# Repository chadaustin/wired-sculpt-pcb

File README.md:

# Design Files for Wired Sculpt Conversion Board

This repository contains the schematic and layout files for the [Microsoft Sculpt Wired Conversion Mod](https://chadaustin.me/2021/02/wired-sculpt/).

## Project Updates

### 2021-09-07

The rev5 board design proposal.

Removed the charge pump.
When the common pin for both LEDs is driven with a 50% duty-cycle rectangular signal both LEDs can be used without additional circuit.
QMK has a feature to change the brightness of background LEDs and we are just going to use this feature to produce such a signal.

As the FN switch is also connected to this line we have to filter out the switching frequency to be able to read the switch.
For this a simple diode rectifier was added. A resistor to discharge the filter capacitor is also needed to detect the switch off state.

### 2021-09-07

The rev4 board design is complete.

When I upgraded the 30-pin ribbon connector to one that fit better, it lowered the resistance to the LEDs. This caused me to burn the microcontroller on a test rev3 board by drawing too much current. So the question became: what values are appropriate for "maximum" brightness on both red and green. Today I found that, given a 5.15V VUSB, whatever resistance in the flex cable, and whatever voltage drop on the LEDs, 150 Ohms gives an even brightness on both red and green. Green draws about 15 mA and red about 10 mA, both within USB low-power spec and the current limits on the microcontroller.

I added an [outputs](outputs/) directory containing the different revisions, and gerber files and drill files generated for either PCBWay or OSH Park.

The biggest challenge right now is the chip shortage. Even some of the capacitors I chose are out of stock. The hardest component to acquire is the ESD protection IC: USBLC6-2SC6. The USBLC6-4SC6 is available, but it would require some tweaking to the PCB layout.

On the software side of things, I added an internal ring buffer for debugging the debouncer. It can be dumped to the HID debug channel by holding both shifts and pressing H. I am trying to figure out why, with my custom low-latency debouncer, sometimes "the" comes out as "theb". For anyone that isn't trying to optimize latency as much as me, you can just run with the default QMK debouncer, which I've never seen produce phantom keys.

### 2021-05-02

One thing that annoyed me about the previous board design was that neither LED was hooked up to a PWM-capable pin and that the green one couldn't be driven, since it wants -5V. I want both lights to work and both to be dimmable.

Rev3 includes a charge pump to produce -5V and two MOSFETs that allow switching the green cathode with PWM.

I also figured out how the Fn switch works: it's a resistor divider that toggles 47K pull-down on a pin with a permanent 1M pull-up. Rev3 includes said 1M pull-up, so the firmware can read the Fn switch's state.

Sadly, it looks like there were many arrangements of media keys on the Sculpt over the years, and most of the media keys have nonsensical icons with behavior that differs on each platform. I'll try to make at least volume and play/pause work.

The parts for board rev 3 arrived last week. Some adjustments were required due to the chip shortage, but it's not too bad. The microcontroller is still available at least.

I attempted assembly of one, and it worked fine, but I screwed up the red and green pins, so I cut some traces and bodged in some kynar wire.

Both lights work!

I have not tested PWM. I did observe that twice as much current is being drawn for each light as I expected. I fear 40 mA could burn out the lights, so I plan to measure an appropriate series resistor this week. It's possible I never had this problem before because I was using a worse-fitting ribbon connector previously. In the past, I always measured 100 Ohms on every pin, but never tested the new ribbon connector.

Also, it kind of sucks that the LED brightness is a function of USB voltage (anywhere between 4.6 V and 5.25 V), but I don't want to include a regulator...

Assembly took about five hours for one board. A lot of that was getting my desk set up. I imagine I could do three boards in ... eight? I think if I used a stencil, hot air assembly could go pretty quickly. Especially if I had a preheater like the MHP30.

A couple people have suggested I set up an Etsy, but if I properly priced in hours of my labor, it would get prohibitive. And I don't want to deal with returns and warranties.

Remaining items before I can say the board is done:
* Order a fourth PCB design with fixed green and red pins
* Include an 0603 resistor on each
* Fix the debouncer
* Add a media key QMK layer, enabled with the Fn switch.

### 2021-04-27

In February, I tried pushing latency further than QMK offers out of the box. I switched from the default debouncer to sym_eager_pk, but since then I've observed some false keydowns and occasionally a phantom keypress. It's common for "the" to produce "theb". (Note that I use the Dvorak key layout.) I haven't looked at the matrix, but it's clear some debouncing is needed on keydown.

I'm planning on writing a custom debouncer that requires at least two frames for a keydown to register and at least 10 ms for a keyup. Having never done AVR optimization, I am trying to get a [simavr](https://github.com/buserror/simavr) benchmark harness up to make sure I don't regress the scan rate.

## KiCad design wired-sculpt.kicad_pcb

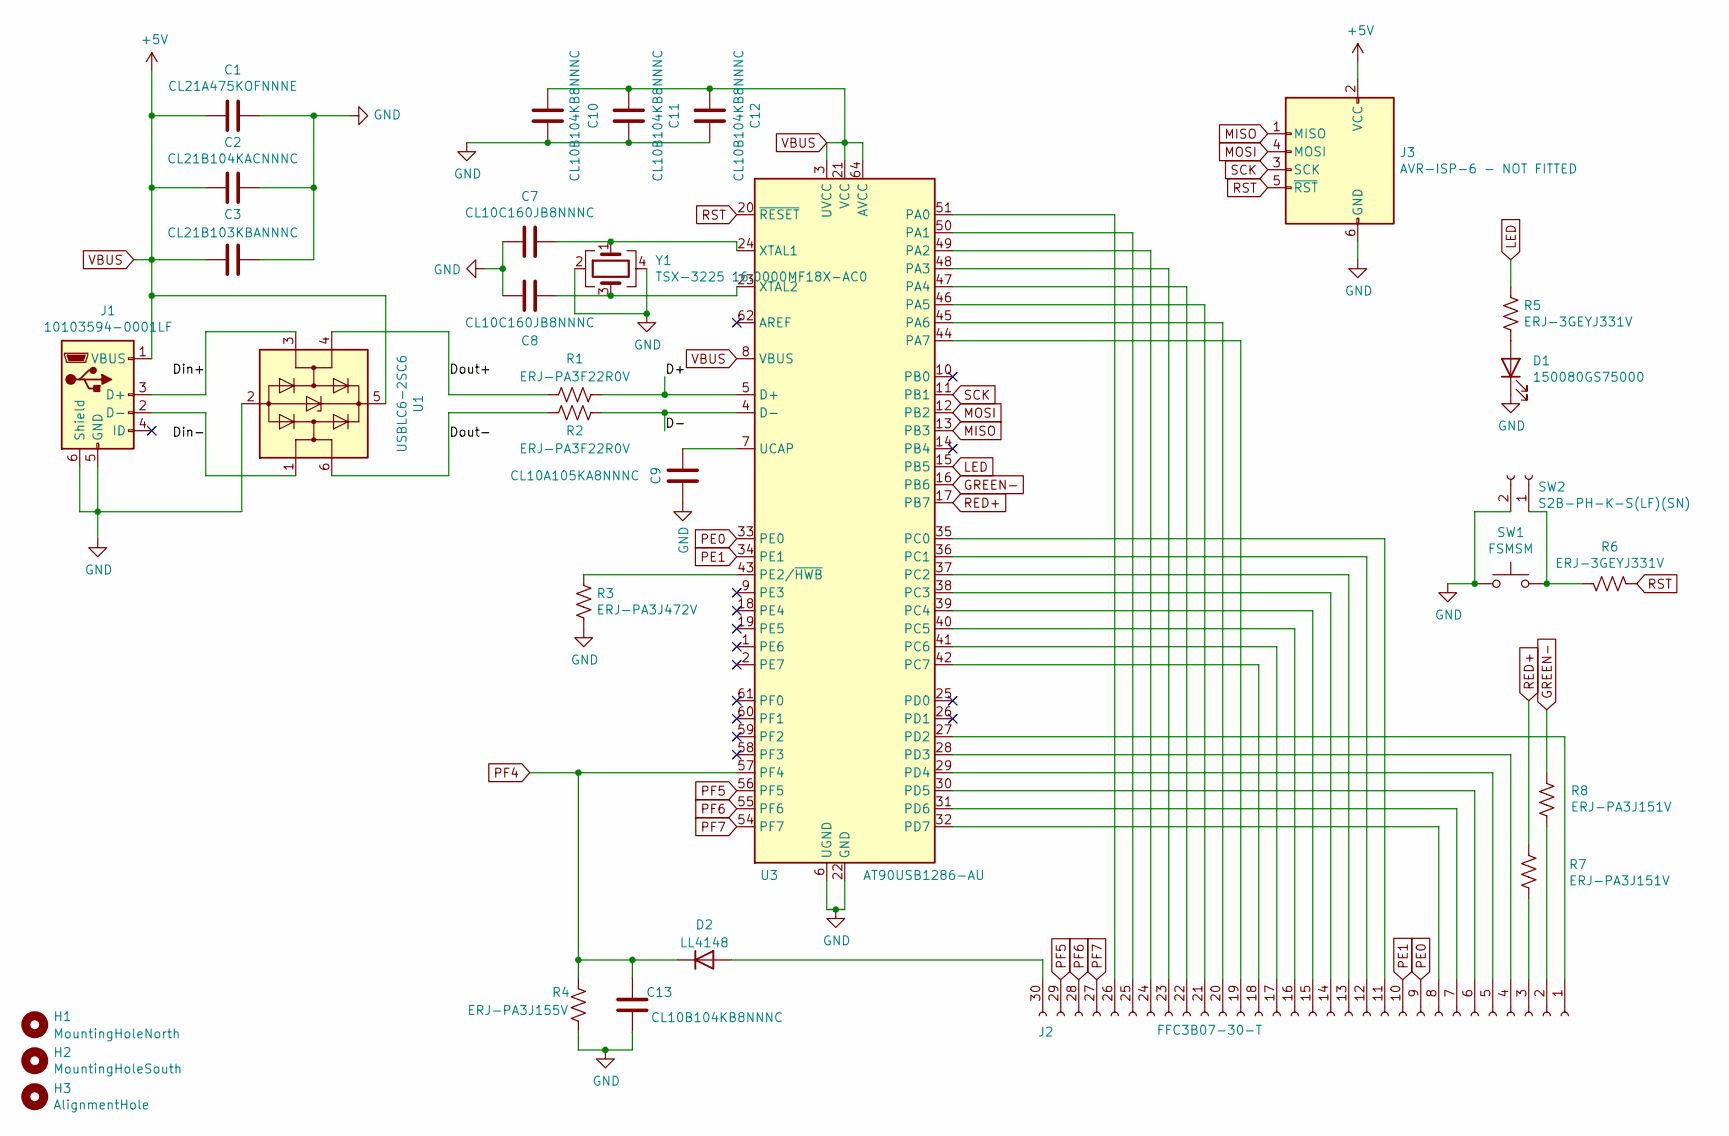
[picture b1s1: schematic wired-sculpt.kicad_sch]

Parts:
C1: CL21A475KOFNNNE; C_0805_2012Metric
C2: CL21B104KACNNNC; C_0805_2012Metric
C3: CL21B103KBANNNC; C_0805_2012Metric
C7, C8: CL10C160JB8NNNC; C_0603_1608Metric
C9: CL10A105KA8NNNC; C_0603_1608Metric
C10, C11, C12, C13: CL10B104KB8NNNC; C_0603_1608Metric
D1: 150080GS75000; LED_0603_1608Metric_Castellated
D2: LL4148; D_MiniMELF
H1: MountingHoleNorth; MountingHole_2.2mm_M2
H2: MountingHoleSouth; MountingHole_2.2mm_M2
H3: AlignmentHole; MountingHole_2.7mm
J1: 10103594-0001LF; USB_Micro-B_Amphenol_10103594-0001LF_Horizontal
J2: FFC3B07-30-T; TE_3-84952-0_1x30-1MP_P1.0mm_Horizontal
J3: AVR-ISP-6 - NOT FITTED; IDC-Header_2x03_P2.54mm_Vertical
R1, R2: ERJ-PA3F22R0V; R_0603_1608Metric
R3: ERJ-PA3J472V; R_0603_1608Metric
R4: ERJ-PA3J155V; R_0603_1608Metric
R5, R6: ERJ-3GEYJ331V; R_0603_1608Metric
R7, R8: ERJ-PA3J151V; R_0603_1608Metric
SW1: FSMSM; SW_SPST_FSMSM
SW2: S2B-PH-K-S(LF)(SN); JST_PH_S2B-PH-K_1x02_P2.00mm_Horizontal
U1: USBLC6-2SC6; SOT-23-6
U3: AT90USB1286-AU; TQFP-64_14x14mm_P0.8mm
Y1: TSX-3225 16.0000MF18X-AC0; Crystal_SMD_3225-4Pin_3.2x2.5mm

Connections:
/D+: R1.1, U3.5 (D+)
/D-: R2.1, U3.4 (D-)
/Din+: J1.3 (D+), U1.3 (I/O2)
/Din-: J1.2 (D-), U1.1 (I/O1)
/Dout+: R1.2, U1.4 (I/O2)
/Dout-: R2.2, U1.6 (I/O1)
GND: C1.1, C2.1, C3.1, C7.2, C8.2, C9.2, C10.1, C11.1, C12.1, C13.1, D1.1 (K), J1.5 (GND), J1.6 (Shield), J3.6 (GND), R3.2, R4.2, SW1.1, SW2.2, U1.2 (GND), U3.6 (UGND), U3.22 (GND), U3.53 (GND), U3.63 (GND), Y1.2, Y1.4
GREEN-: R8.1, U3.16 (PB6)
LED: R5.1, U3.15 (PB5)
MISO: J3.1 (MISO), U3.13 (PB3)
MOSI: J3.4 (MOSI), U3.12 (PB2)
unnamed: C7.1, U3.24 (XTAL1), Y1.1
unnamed: C8.1, U3.23 (XTAL2), Y1.3
unnamed: C9.1, U3.7 (UCAP)
unnamed: D1.2 (A), R5.2
unnamed: J2.1, U3.27 (PD2)
unnamed: J2.2, R8.2
unnamed: J2.3, R7.2
unnamed: J2.4, U3.28 (PD3)
unnamed: J2.5, U3.29 (PD4)
unnamed: J2.6, U3.30 (PD5)
unnamed: J2.7, U3.31 (PD6)
unnamed: J2.8, U3.32 (PD7)
unnamed: J2.11, U3.35 (PC0)
unnamed: J2.12, U3.36 (PC1)
unnamed: J2.13, U3.37 (PC2)
unnamed: J2.14, U3.38 (PC3)
unnamed: J2.15, U3.39 (PC4)
unnamed: J2.16, U3.40 (PC5)
unnamed: J2.17, U3.41 (PC6)
unnamed: J2.18, U3.42 (PC7)
unnamed: J2.19, U3.44 (PA7)
unnamed: J2.20, U3.45 (PA6)
unnamed: J2.21, U3.46 (PA5)
unnamed: J2.22, U3.47 (PA4)
unnamed: J2.23, U3.48 (PA3)
unnamed: J2.24, U3.49 (PA2)
unnamed: J2.25, U3.50 (PA1)
unnamed: J2.26, U3.51 (PA0)
unnamed: D2.2 (A), J2.30
unnamed: R3.1, U3.43 (PE2/~HWB)
unnamed: R6.2, SW1.2, SW2.1
PE0: J2.9, U3.33 (PE0)
PE1: J2.10, U3.34 (PE1)
PF4: C13.2, D2.1 (K), R4.1, U3.57 (PF4)
PF5: J2.29, U3.56 (PF5)
PF6: J2.28, U3.55 (PF6)
PF7: J2.27, U3.54 (PF7)
RED+: R7.1, U3.17 (PB7)
RST: J3.5 (~RST), R6.1, U3.20 (~RESET)
SCK: J3.3 (SCK), U3.11 (PB1)
VBUS: C1.2, C2.2, C3.2, C10.2, C11.2, C12.2, J1.1 (VBUS), J3.2 (VCC), U1.5 (VBUS), U3.3 (UVCC), U3.8 (VBUS), U3.21 (VCC), U3.52 (VCC), U3.64 (AVCC)

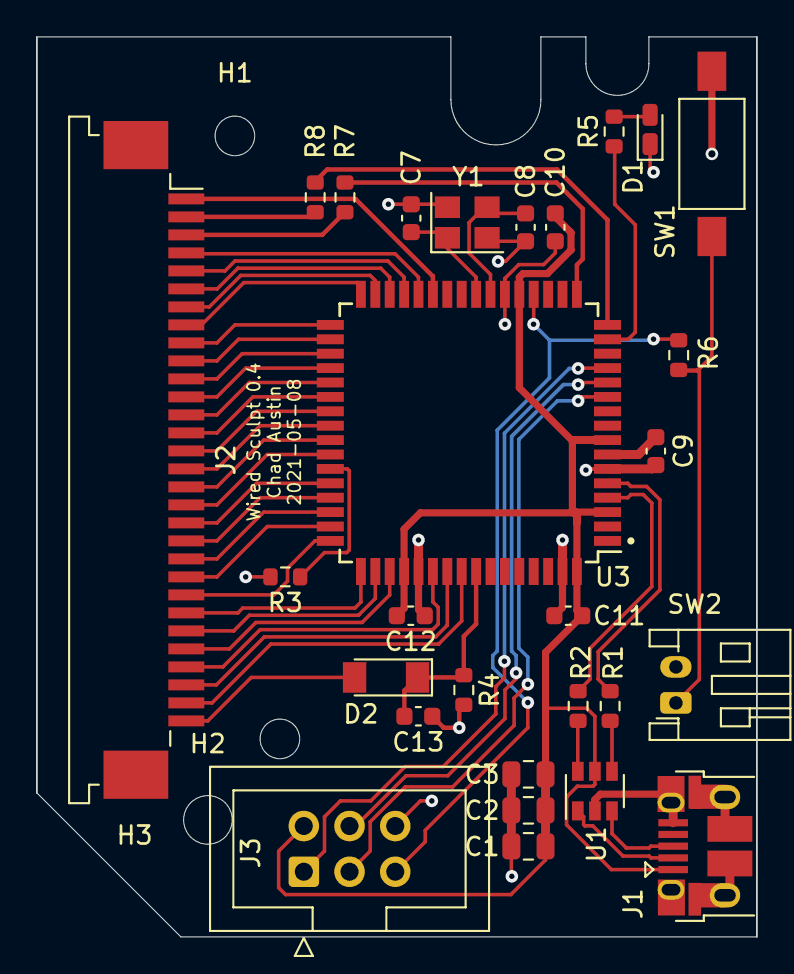
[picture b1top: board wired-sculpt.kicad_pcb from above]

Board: 2 copper layers, 40.0 x 50.0 mm, 31 parts (0 on the bottom side), 52 nets.

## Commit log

2021-02-20 0.2 design files
2021-04-18 WIP: checkpoint work on rev 3 of the schematic and layout
2021-04-18 renumber the references
2021-04-19 Move a trace and generate gerbers for Apr 18
2021-05-02 fit the schematic on US Letter paper instead of A4
2021-05-03 Fix Green- and Red+ pins which were backwards. :(
2021-05-03 project updates
2021-05-09 add two resistors for the LEDs: this ribbon cable connector must have lower resistance
2021-05-09 chip shortage part substitutions
2021-07-11 change resistor values for LEDs
2021-09-07 set red and green current-limiting resistors to 150R
2021-09-07 add 0.4 revision board gerbers for osh park
2021-09-08 move outputs into named directories
2021-09-08 add a rev4 output for PCBWay
2021-09-08 2021-09-07 project update
2023-03-24 The rev5 board design proposal.
    Removed the charge pump.
    When the common pin for both LEDs is driven with a 50% duty-cycle rectangular signal both LEDs can be used without additional circuit.
    QMK has a feature to change the brightness of background LEDs and we are just going to use this feature to produce such a signal.
    As the FN switch is also connected to this line we have to filter out the switching frequency to be able to read the switch.
    For this a simple diode rectifier was added. A resistor to discharge the filter capacitor is also needed to detect the switch off state.
